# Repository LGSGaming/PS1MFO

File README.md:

# PS1MFO
 A multifrequency oscillator for the PS1

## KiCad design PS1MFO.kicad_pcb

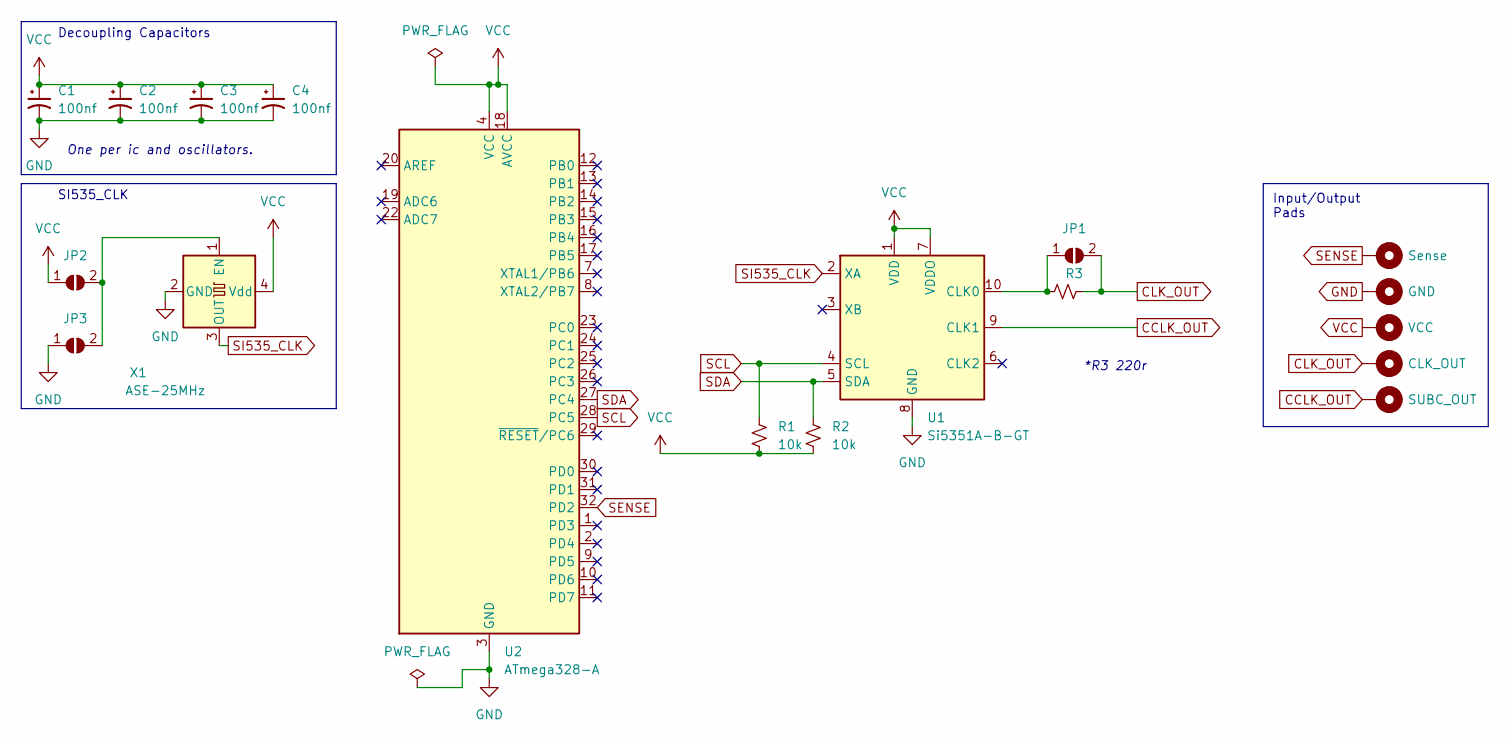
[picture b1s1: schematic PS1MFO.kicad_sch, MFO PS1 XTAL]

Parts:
C1, C2, C3, C4: 100nf; C_0201_0603Metric_Pad0.64x0.40mm_HandSolder
H7: Sense; TestPoint_Pad_1.0x1.0mm
H8: GND; TestPoint_Pad_1.0x1.0mm
H9: VCC; TestPoint_Pad_1.0x1.0mm
H10: CLK_OUT; TestPoint_Pad_1.0x1.0mm
H11: SUBC_OUT; TestPoint_Pad_1.0x1.0mm
JP1, JP2, JP3: SolderJumper_2_Open; SolderJumper-2_P1.3mm_Open_RoundedPad1.0x1.5mm
R1, R2: 10k; R_0201_0603Metric_Pad0.64x0.40mm_HandSolder
R3: 220r; R_0201_0603Metric_Pad0.64x0.40mm_HandSolder
U1: Si5351A-B-GT; MSOP-10_3x3mm_P0.5mm
U2: ATmega328-A; TQFP-32_7x7mm_P0.8mm
X1: ASE-25MHz; Oscillator_SMD_Abracon_ASE-4Pin_3.2x2.5mm

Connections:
CCLK_OUT: H11.1, U1.9 (CLK1)
CLK_OUT: H10.1, JP1.2 (B), R3.2
GND: C1.2, C2.2, C3.2, C4.2, H8.1, JP3.1 (A), U1.8 (GND), U2.3 (GND), U2.5 (GND), U2.21 (GND), X1.2 (GND)
unnamed: JP1.1 (A), R3.1, U1.10 (CLK0)
unnamed: JP2.2 (B), JP3.2 (B), X1.1 (EN)
SCL: R1.2, U1.4 (SCL), U2.28 (PC5)
SDA: R2.2, U1.5 (SDA), U2.27 (PC4)
SENSE: H7.1, U2.32 (PD2)
SI535_CLK: U1.2 (XA), X1.3 (OUT)
VCC: C1.1, C2.1, C3.1, C4.1, H9.1, JP2.1 (A), R1.1, R2.1, U1.1 (VDD), U1.7 (VDDO), U2.4 (VCC), U2.6 (VCC), U2.18 (AVCC), X1.4 (Vdd)

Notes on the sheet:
SI535_CLK
One per ic and oscillators.
Decoupling Capacitors
*R3 220r
Input/Output Pads

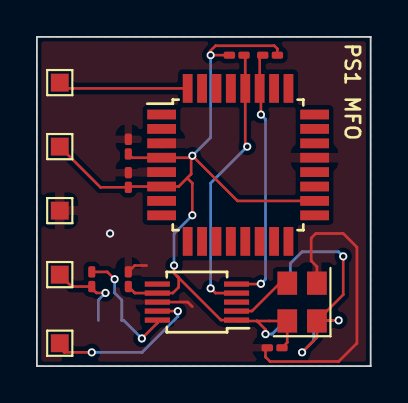
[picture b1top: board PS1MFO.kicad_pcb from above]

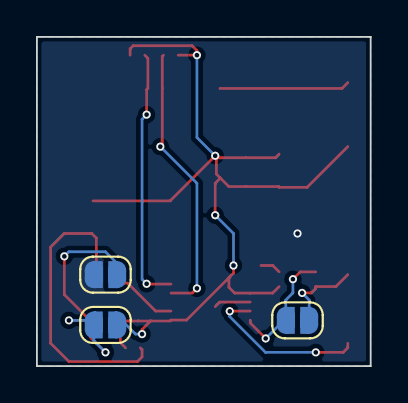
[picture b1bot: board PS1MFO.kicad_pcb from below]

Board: 2 copper layers, 18.5 x 18.3 mm, 18 parts (3 on the bottom side), 10 nets.

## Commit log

2024-04-27 Initial commit
    First
